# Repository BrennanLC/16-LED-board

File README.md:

# 16-LED-board
This is a KiCAD design project for 16 LED board

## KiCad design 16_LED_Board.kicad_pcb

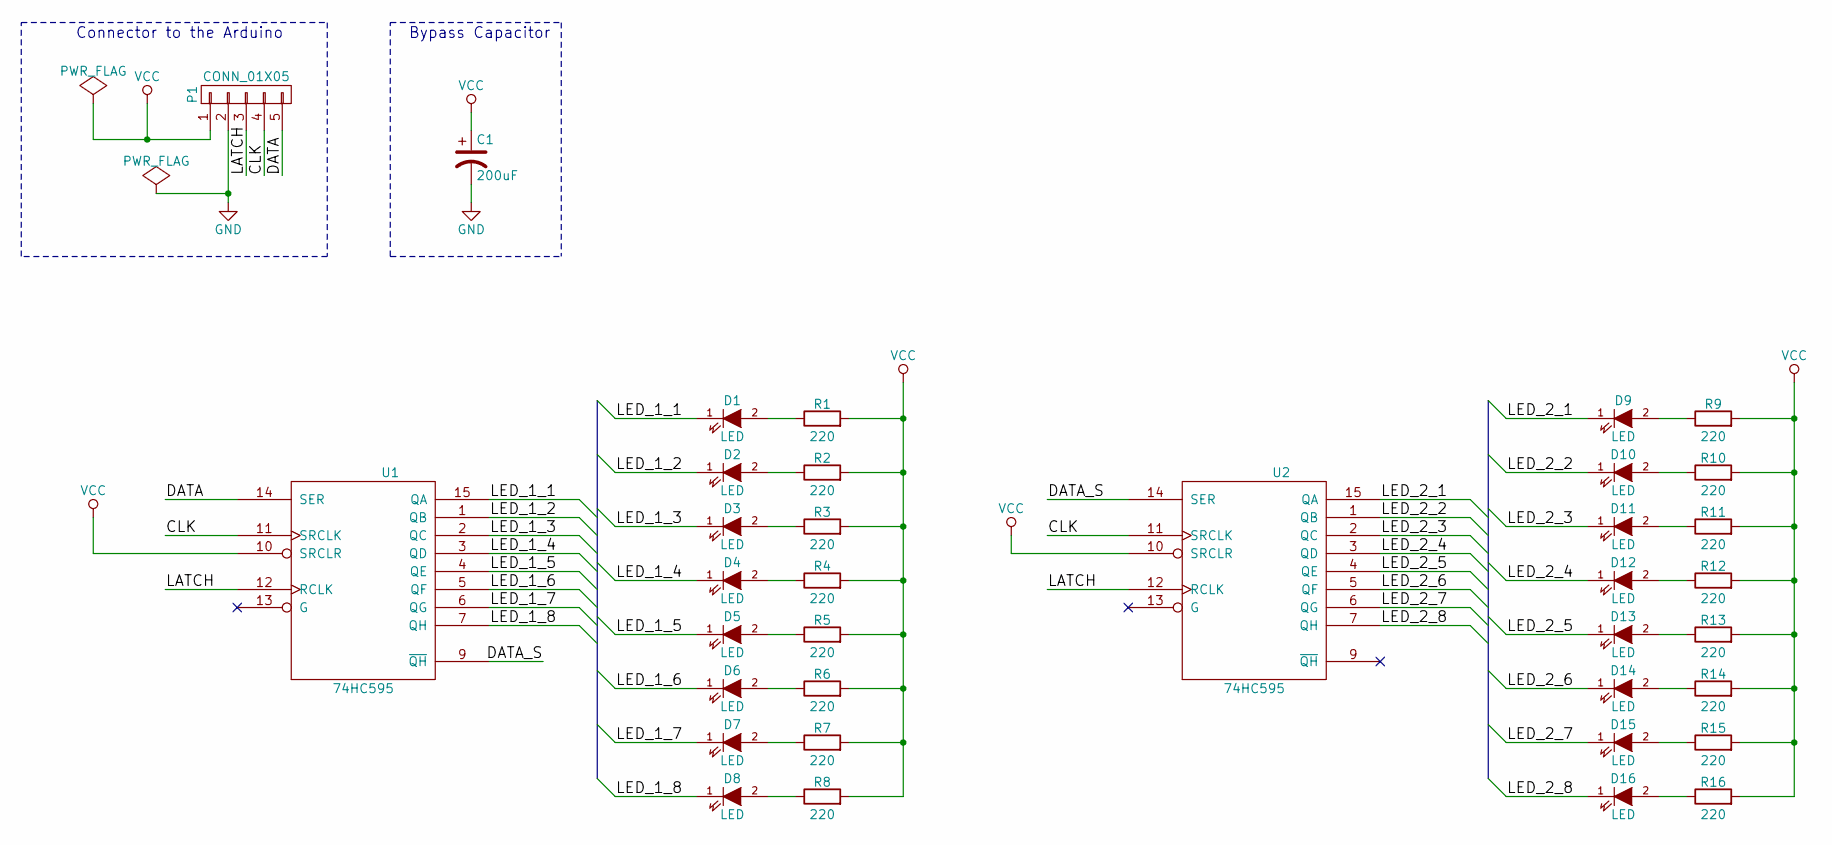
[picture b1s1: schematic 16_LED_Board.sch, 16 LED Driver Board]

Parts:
C1: 200uF; c_elec_6.3x5.3
D1, D2, D3, D4, D5, D6, D7, D8, D9, D10, D11, D12, D13, D14, D15, D16: LED; LED_0805
P1: CONN_01X05; Pin_Header_Straight_1x05
R1, R2, R3, R4, R5, R6, R7, R8, R9, R10, R11, R12, R13, R14, R15, R16: 220; R_0805_HandSoldering
U1, U2: 74HC595; SO-16-N

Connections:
/CLK: P1.4, U1.11 (SRCLK), U2.11 (SRCLK)
/DATA: P1.5, U1.14 (SER)
/DATA_S: U1.9 (~QH), U2.14 (SER)
/LATCH: P1.3, U1.12 (RCLK), U2.12 (RCLK)
/LED_1_1: D1.1 (K), U1.15 (QA)
/LED_1_2: D2.1 (K), U1.1 (QB)
/LED_1_3: D3.1 (K), U1.2 (QC)
/LED_1_4: D4.1 (K), U1.3 (QD)
/LED_1_5: D5.1 (K), U1.4 (QE)
/LED_1_6: D6.1 (K), U1.5 (QF)
/LED_1_7: D7.1 (K), U1.6 (QG)
/LED_1_8: D8.1 (K), U1.7 (QH)
/LED_2_1: D9.1 (K), U2.15 (QA)
/LED_2_2: D10.1 (K), U2.1 (QB)
/LED_2_3: D11.1 (K), U2.2 (QC)
/LED_2_4: D12.1 (K), U2.3 (QD)
/LED_2_5: D13.1 (K), U2.4 (QE)
/LED_2_6: D14.1 (K), U2.5 (QF)
/LED_2_7: D15.1 (K), U2.6 (QG)
/LED_2_8: D16.1 (K), U2.7 (QH)
GND: C1.2, P1.2, U1.8 (GND), U2.8 (GND)
unnamed: D1.2 (A), R1.1
unnamed: D2.2 (A), R2.1
unnamed: D3.2 (A), R3.1
unnamed: D4.2 (A), R4.1
unnamed: D5.2 (A), R5.1
unnamed: D6.2 (A), R6.1
unnamed: D7.2 (A), R7.1
unnamed: D8.2 (A), R8.1
unnamed: D9.2 (A), R9.1
unnamed: D10.2 (A), R10.1
unnamed: D11.2 (A), R11.1
unnamed: D12.2 (A), R12.1
unnamed: D13.2 (A), R13.1
unnamed: D14.2 (A), R14.1
unnamed: D15.2 (A), R15.1
unnamed: D16.2 (A), R16.1
VCC: C1.1, P1.1, R1.2, R2.2, R3.2, R4.2, R5.2, R6.2, R7.2, R8.2, R9.2, R10.2, R11.2, R12.2, R13.2, R14.2, R15.2, R16.2, U1.10 (SRCLR), U1.16 (VCC), U2.10 (SRCLR), U2.16 (VCC)

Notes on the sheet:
Connector to the Arduino
Bypass Capacitor

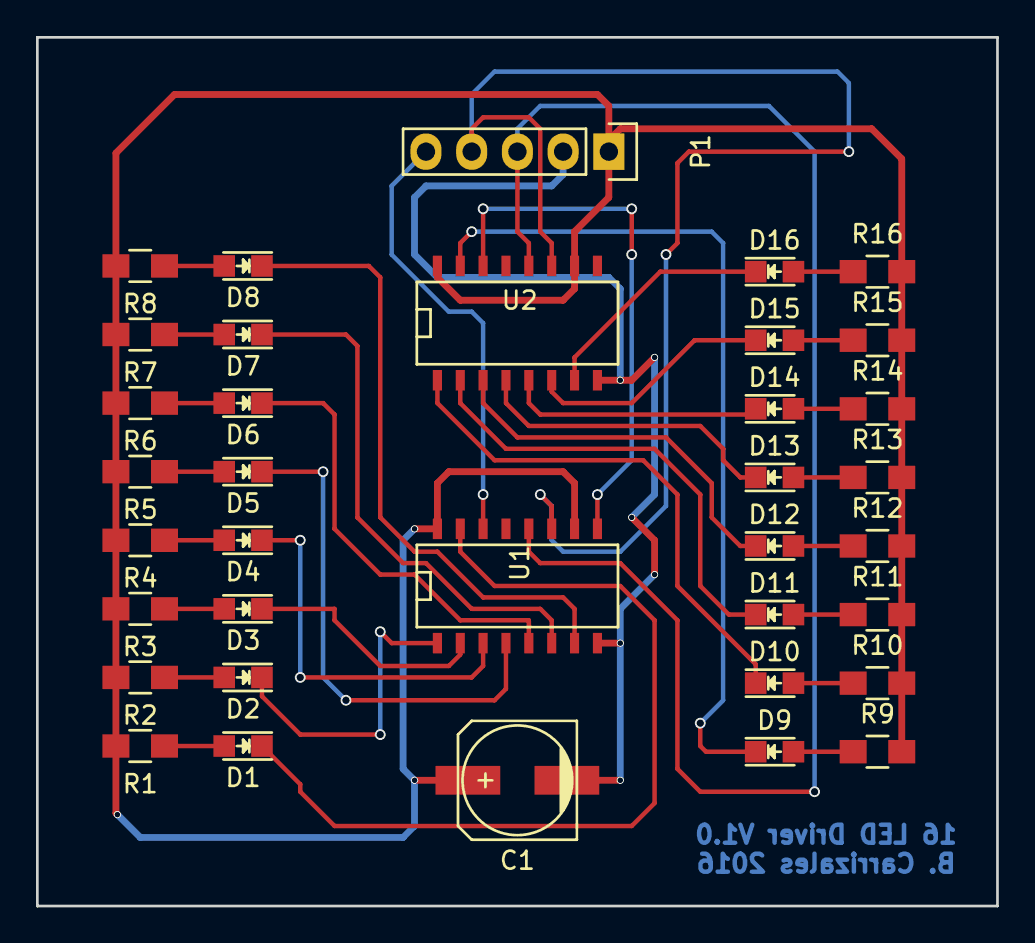
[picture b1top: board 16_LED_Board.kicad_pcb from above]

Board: 2 copper layers, 53.3 x 48.3 mm, 36 parts (0 on the bottom side), 38 nets.

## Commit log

2016-09-05 Update .gitignore
    Removed .net, .xml and .csv files from listing
2016-09-06 Add Initial Project Files
    This commit adds initial project files to the repository.
